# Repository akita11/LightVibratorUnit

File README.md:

# LightVibratorUnit

円形振動モータで振動を発生するUnitです。与える制御信号のPWM比で振動の強さを制御できます。※[M5Stack純正の振動モータユニット](https://www.switch-science.com/products/6065)は振動が強すぎるため、UIFlowの"Vibrator"のブロックは強さを20までしか設定できません。そのため本ユニットを使う場合は、UIFlowのPWMブロックを使って制御してください。

## ピン配置

Grove端子の1番から順に「無接続」「振動モータ制御」「VDD(5V/3.3V)」「GND」の順です。

## Author

Junichi Akita (akita@ifdl.jp, @akita11)

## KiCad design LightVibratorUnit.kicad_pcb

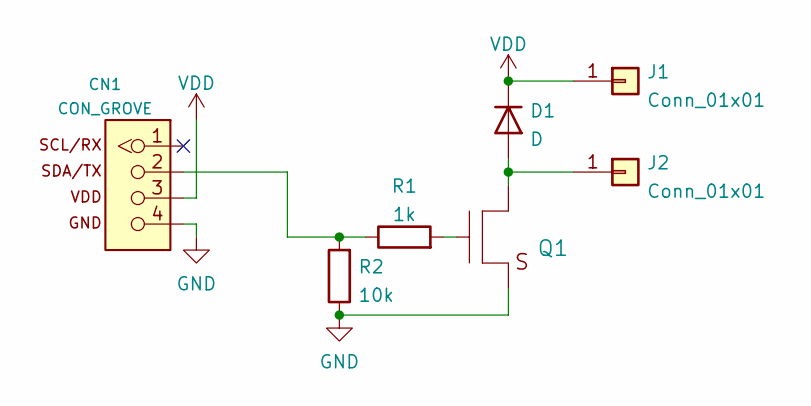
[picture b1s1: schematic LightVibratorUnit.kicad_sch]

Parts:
CN1: CON_GROVE; CON_GROVE_H
D1: D; D_SOD-123F
J1, J2: Conn_01x01; Pad_TH09mm
Q1: TR_NMOS_IRLML6344; SOT-23
R1: 1k; R_0603_1608Metric
R2: 10k; R_0603_1608Metric

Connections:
GND: CN1.4, Q1.2 (S), R2.1
unnamed: CN1.2, R1.1, R2.2
unnamed: D1.2 (A), J2.1, Q1.3 (D)
unnamed: Q1.1 (G), R1.2
VDD: CN1.3, D1.1 (K), J1.1

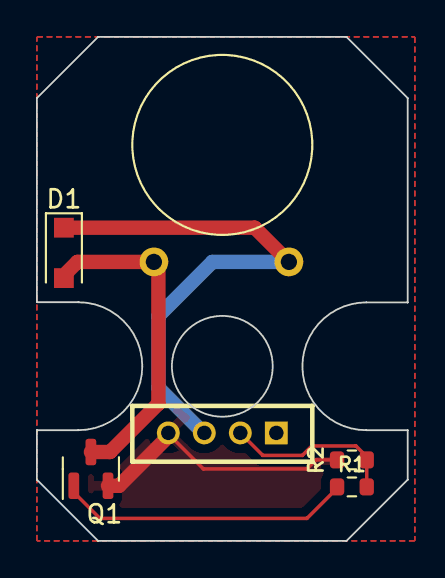
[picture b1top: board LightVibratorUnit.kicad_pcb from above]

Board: 2 copper layers, 20.6 x 28.0 mm, 7 parts (0 on the bottom side), 5 nets.

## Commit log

2024-03-23 update photo
